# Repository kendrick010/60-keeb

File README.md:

# 60-keeb
> A 60% keyboard because why not.

## How To...
Stack Order:
- plate_1 (top most)
- plate_2
- plate_3 (switch plate)
- plate_4
- plate_5
- plate_6 (bottom most)

## BOM
| Component | Vendor | Quantity|
| --------- | ------ | ------- |
| PCB | -------- | 1 |
| ATMEGA32U4 | [Digikey](https://www.digikey.com/en/products/detail/microchip-technology/ATMEGA32U4RC-MUR/2507985) | 1 |
| USB Mini B Port | [Digikey](https://www.digikey.com/en/products/detail/edac-inc/690-005-299-043/4312191) | 1 |
| Tactile SMD Switch | [Digikey](https://www.digikey.com/en/products/detail/e-switch/TL3342F160QG-TR/379004) | 1 |
| 1N4148 SMD Diode | [Digikey](https://www.digikey.com/en/products/detail/smc-diode-solutions/1N4148WTR/6022450) | 63 |
| 16MHz SMD Cystal | [Digikey](https://www.digikey.com/en/products/detail/ecs-inc./ECS-160-12-33-AGM-TR/9648950?utm_adgroup=Crystals&utm_source=google&utm_medium=cpc&utm_campaign=Shopping_Product_Crystals%2C%20Oscillators%2C%20Resonators_NEW&utm_term=&utm_content=Crystals&gclid=CjwKCAjwloCSBhAeEiwA3hVo_cbyDTwI6-S_fugYXFgKN49tR0nGhBOCDoLL6SpNIffyFdOyPNAKBRoCRlkQAvD_BwE) | 1 |
| 22Ω SMD Resistor | [Digikey](https://www.digikey.com/en/products/detail/stackpole-electronics-inc/RMCF0805JT22R0/1942533) | 2 |
| 10kΩ SMD Resistor | [Digikey](https://www.digikey.com/en/products/detail/stackpole-electronics-inc/RMCF0805JT10K0/1942577) | 2 |
| 0.1uF Ceramic SMD Capacitor | [Digikey](https://www.digikey.com/en/products/detail/kyocera-avx/08055F104K4T2A/1024871?s=N4IgTCBcDaICwHYAcBaAzANgIxxVlAcgCIgC6AvkA) | 4 |
| 1uF Ceramic SMD Capacitor | [Digikey](https://www.digikey.com/en/products/detail/yageo/CC0805KKX7R8BB105/2833621) | 1 |
| 4.7uF Ceramic SMD Capacitor | [Digikey](https://www.digikey.com/en/products/detail/samsung-electro-mechanics/CL21A475KAQNNNE/3886902) | 1 |
| 22pF Ceramic SMD Capacitor | [Digikey](https://www.digikey.com/en/products/detail/kemet/C0805C220J5GACTU/411388) | 2 |
| M2x16mm Standoffs | [Amazon](https://www.amazon.com/dp/B07768Q7YS?psc=1&ref=ppx_yo2ov_dt_b_product_details) | 8 |
| M2 Screws | [Amazon](https://www.amazon.com/dp/B07768Q7YS?psc=1&ref=ppx_yo2ov_dt_b_product_details) | 8 |

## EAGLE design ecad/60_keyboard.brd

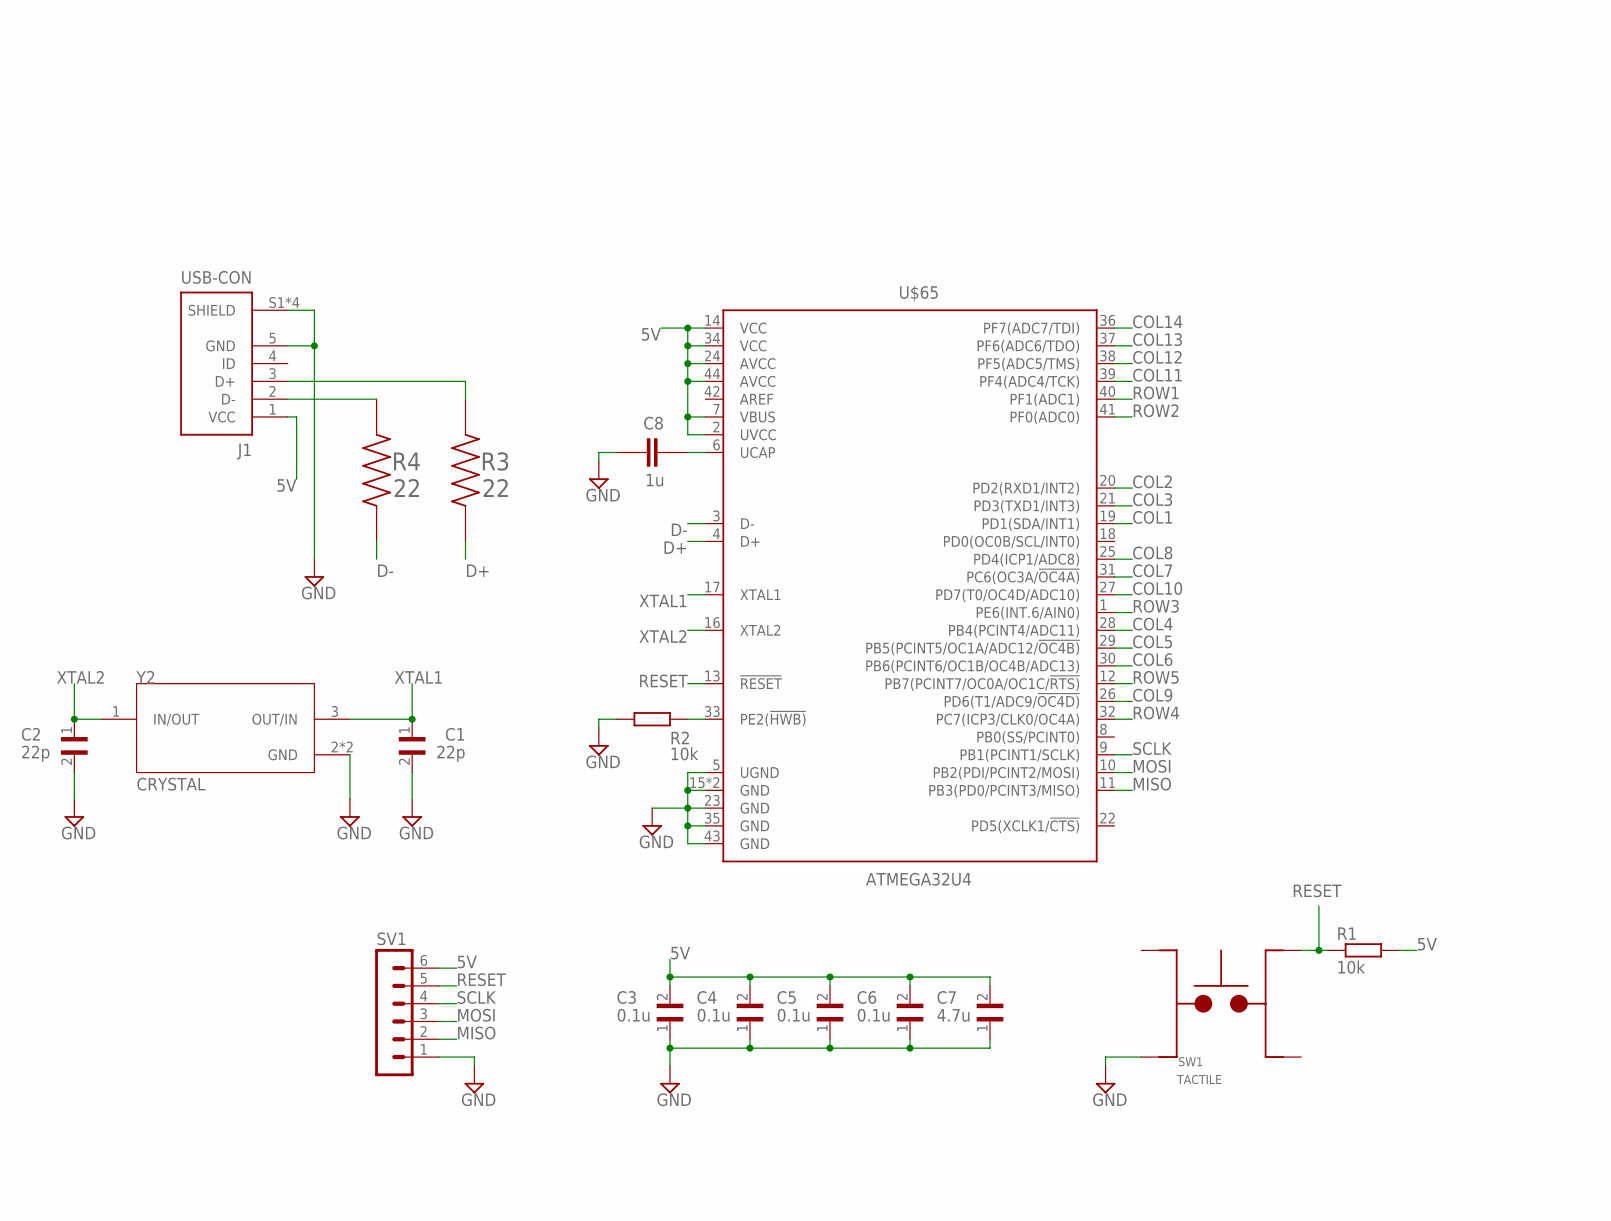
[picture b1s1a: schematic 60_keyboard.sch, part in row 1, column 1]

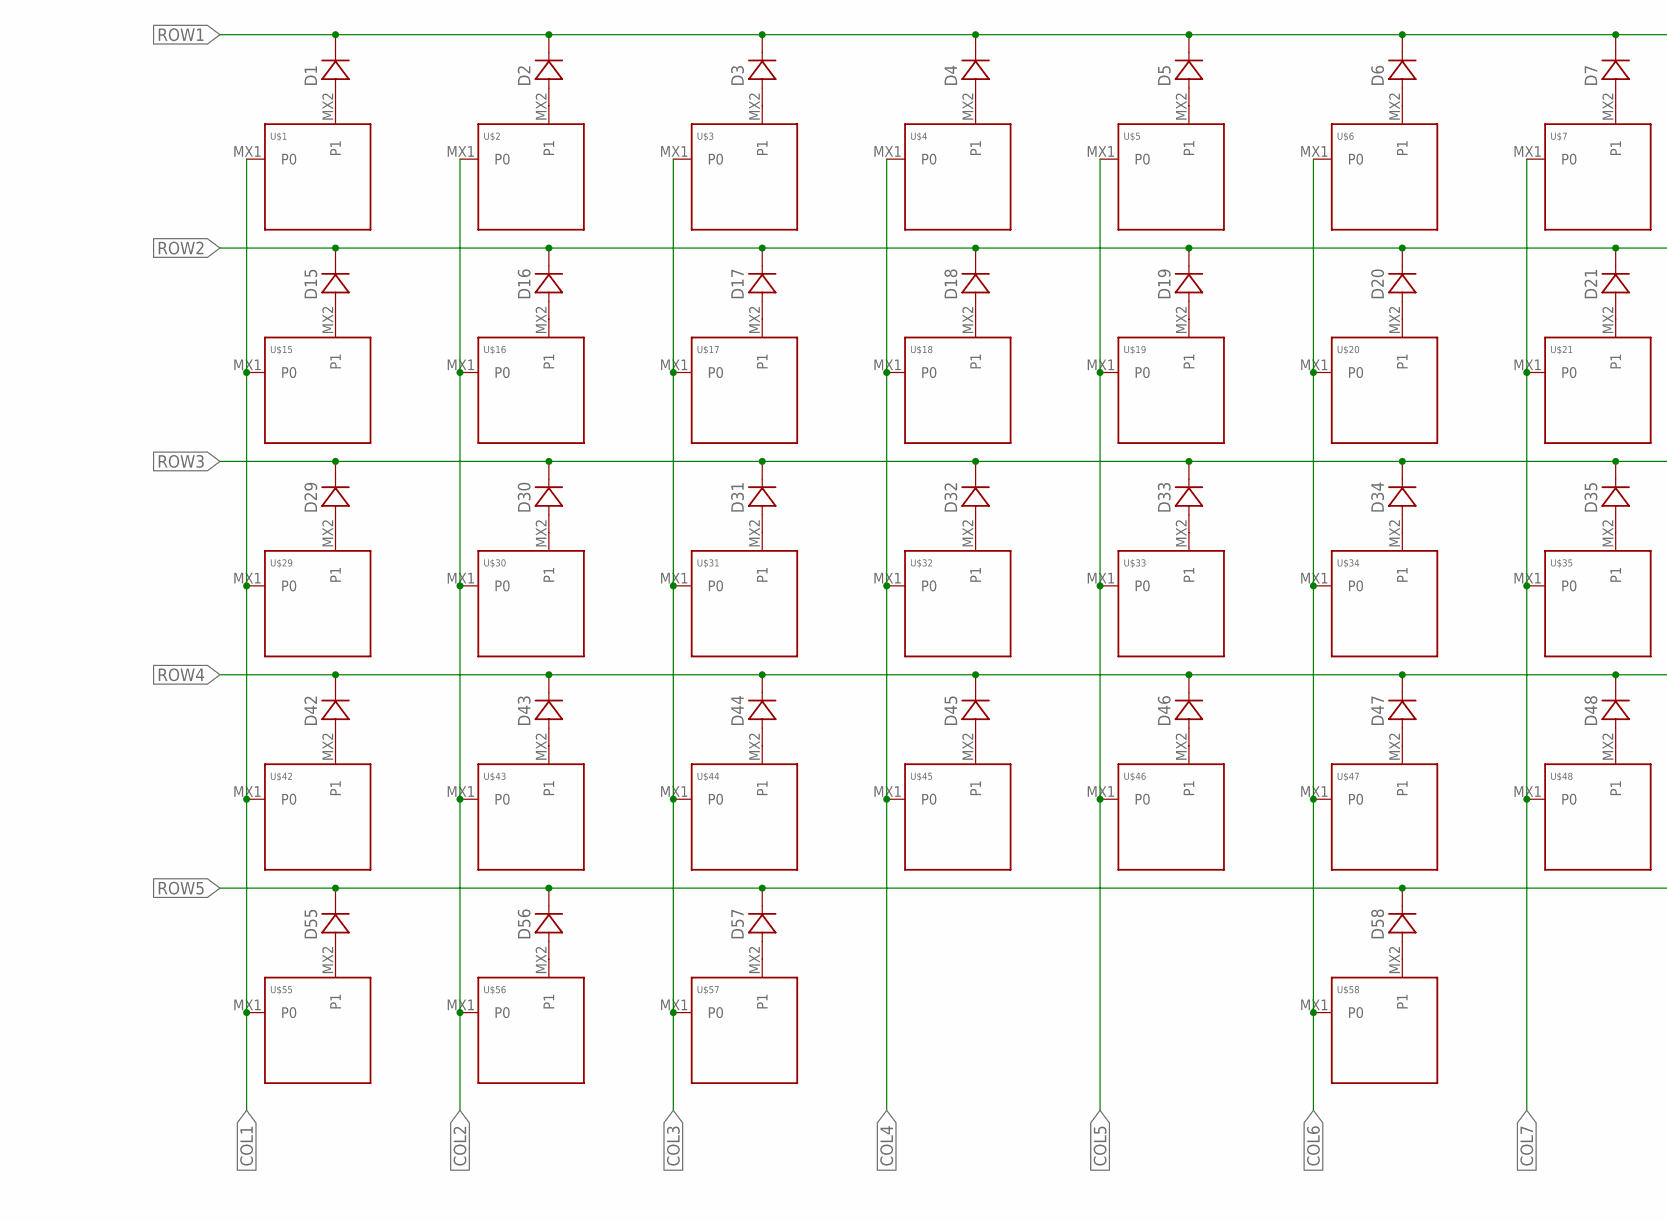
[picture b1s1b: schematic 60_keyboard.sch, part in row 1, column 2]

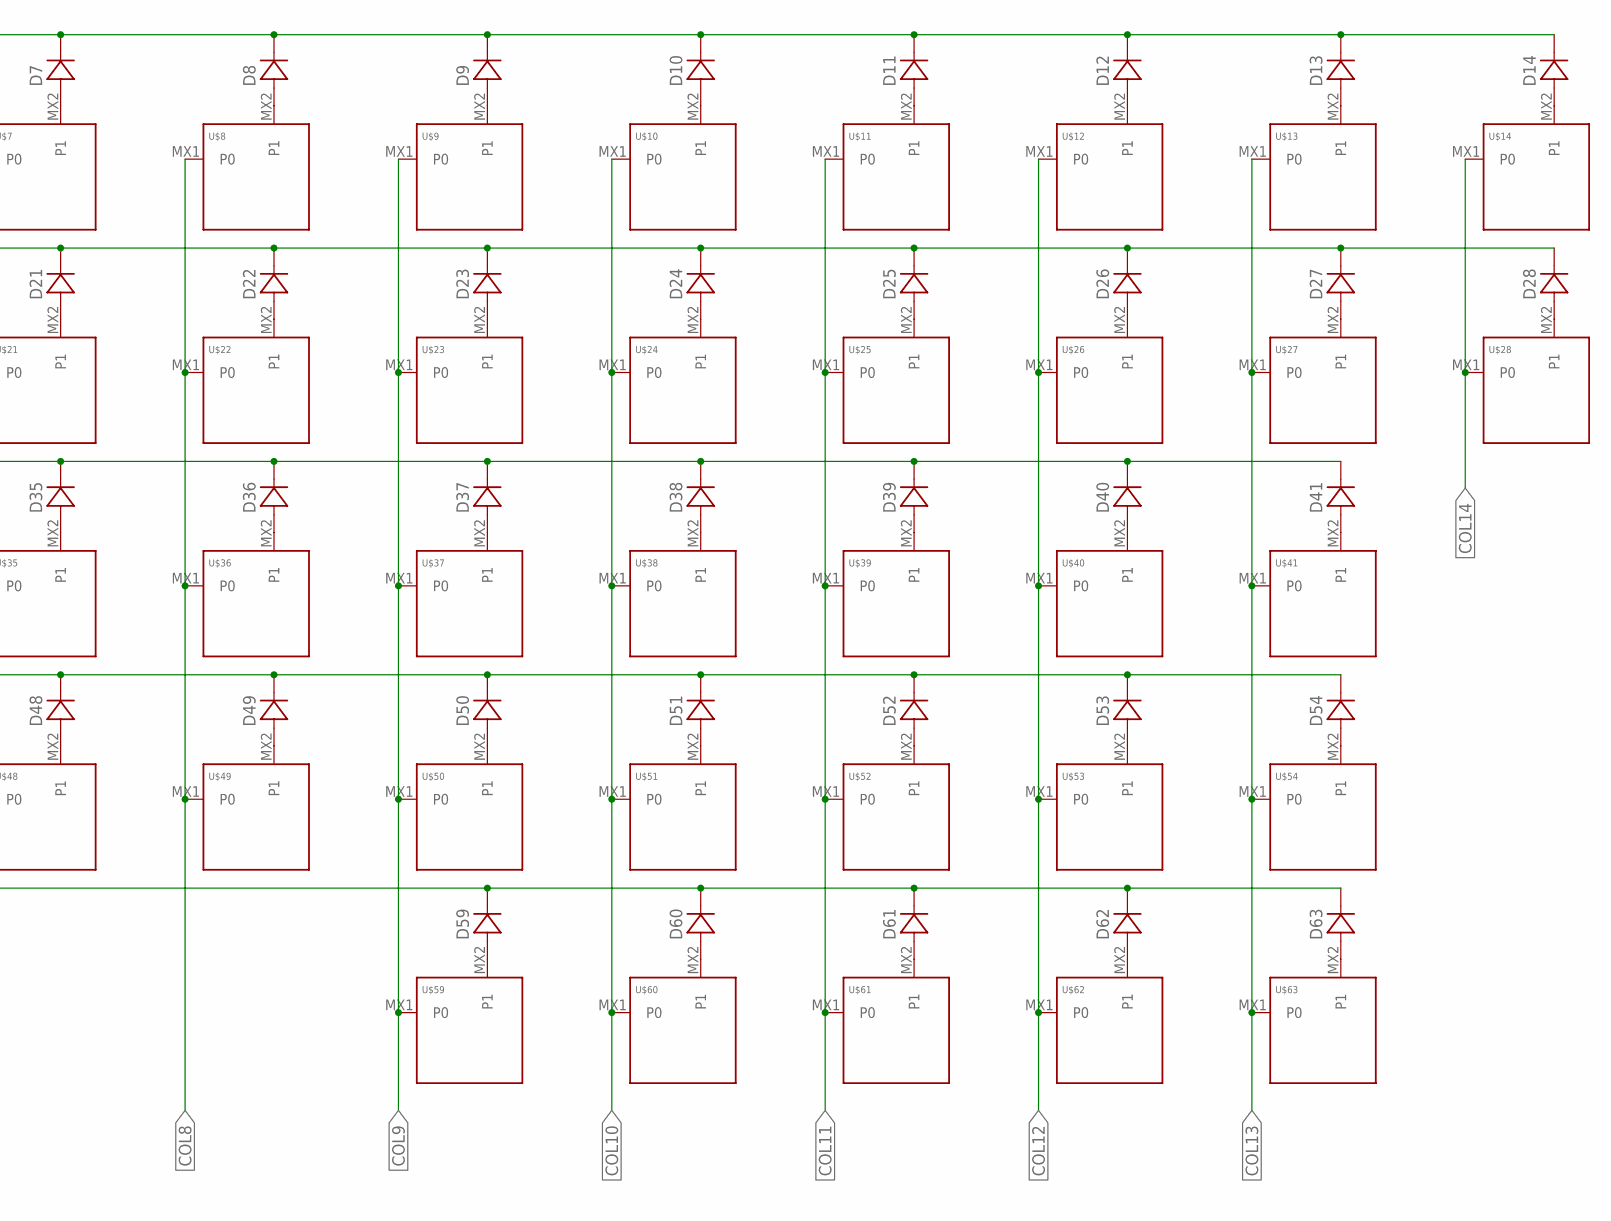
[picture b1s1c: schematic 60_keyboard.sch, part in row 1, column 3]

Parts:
C1, C2: 22p; CAPC2012X140N
C3, C4, C5, C6: 0.1u; CAPC2012X140N
C7: 4.7u; CAPC2012X140N
C8: 1u; C0805
D1, D2, D3, D4, D5, D6, D7, D8, D9, D10, D11, D12, D13, D14, D15, D16, D17, D18, D19, D20, D21, D22, D23, D24, D25, D26, D27, D28, D29, D30, D31, D32, D33, D34, D35, D36, D37, D38, D39, D40, D41, D42, D43, D44, D45, D46, D47, D48, D49, D50, D51, D52, D53, D54, D55, D56, D57, D58, D59, D60, D61, D62, D63: DIODE-SOD-123; SOD-123
J1: USB-CON; EDAC_690-005-299-043
R1, R2: 10k; R0805
R3, R4: 22; RESC2012X65N
SV1: MA06-1
SW1: TACTILE; SW_TL3342F160QG/TR
U$1, U$2, U$3, U$4, U$5, U$6, U$7, U$8, U$9, U$10, U$11, U$12, U$13, U$15, U$16, U$17, U$18, U$19, U$20, U$21, U$22, U$23, U$24, U$25, U$26, U$27, U$28, U$29, U$30, U$31, U$32, U$33, U$34, U$35, U$36, U$37, U$38, U$39, U$40, U$43, U$44, U$45, U$46, U$47, U$48, U$49, U$50, U$51, U$52, U$53, U$54, U$55, U$56, U$57, U$59, U$60, U$61, U$62, U$63: KEYSWITCH-PLAIN-MXHSPCB-1U; MXHSPCB-1U
U$14, U$41, U$42: KEYSWITCH-PLAIN-MXHSPCB-2U; MXHSPCB-2U
U$58: KEYSWITCH-PLAIN-MXHSPCB-6.25U-FLIPPED; MXHSPCB-6.25U-FLIPPED
U$65: ATMEGA32U4; QFN-44
Y2: CRYSTAL; XTAL_ECS-160-12-33-AGN-TR

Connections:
5V: C3.2, C4.2, C5.2, C6.2, C7.2, J1.1 (VCC), R1.2, SV1.6, U$65.2 (UVCC), U$65.7 (VBUS), U$65.14 (VCC), U$65.24 (AVCC), U$65.34 (VCC), U$65.44 (AVCC)
COL1: U$1.MX1 (P0), U$15.MX1 (P0), U$29.MX1 (P0), U$42.MX1 (P0), U$55.MX1 (P0), U$65.19 (PD1(SDA/INT1))
COL2: U$2.MX1 (P0), U$16.MX1 (P0), U$30.MX1 (P0), U$43.MX1 (P0), U$56.MX1 (P0), U$65.20 (PD2(RXD1/INT2))
COL3: U$3.MX1 (P0), U$17.MX1 (P0), U$31.MX1 (P0), U$44.MX1 (P0), U$57.MX1 (P0), U$65.21 (PD3(TXD1/INT3))
COL4: U$4.MX1 (P0), U$18.MX1 (P0), U$32.MX1 (P0), U$45.MX1 (P0), U$65.28 (PB4(PCINT4/ADC11))
COL5: U$5.MX1 (P0), U$19.MX1 (P0), U$33.MX1 (P0), U$46.MX1 (P0), U$65.29 (PB5(PCINT5/OC1A/ADC12/!OC4B))
COL6: U$6.MX1 (P0), U$20.MX1 (P0), U$34.MX1 (P0), U$47.MX1 (P0), U$58.MX1 (P0), U$65.30 (PB6(PCINT6/OC1B/OC4B/ADC13))
COL7: U$7.MX1 (P0), U$21.MX1 (P0), U$35.MX1 (P0), U$48.MX1 (P0), U$65.31 (PC6(OC3A/!OC4A))
COL8: U$8.MX1 (P0), U$22.MX1 (P0), U$36.MX1 (P0), U$49.MX1 (P0), U$65.25 (PD4(ICP1/ADC8))
COL9: U$9.MX1 (P0), U$23.MX1 (P0), U$37.MX1 (P0), U$50.MX1 (P0), U$59.MX1 (P0), U$65.26 (PD6(T1/ADC9/!OC4D))
COL10: U$10.MX1 (P0), U$24.MX1 (P0), U$38.MX1 (P0), U$51.MX1 (P0), U$60.MX1 (P0), U$65.27 (PD7(T0/OC4D/ADC10))
COL11: U$11.MX1 (P0), U$25.MX1 (P0), U$39.MX1 (P0), U$52.MX1 (P0), U$61.MX1 (P0), U$65.39 (PF4(ADC4/TCK))
COL12: U$12.MX1 (P0), U$26.MX1 (P0), U$40.MX1 (P0), U$53.MX1 (P0), U$62.MX1 (P0), U$65.38 (PF5(ADC5/TMS))
COL13: U$13.MX1 (P0), U$27.MX1 (P0), U$41.MX1 (P0), U$54.MX1 (P0), U$63.MX1 (P0), U$65.37 (PF6(ADC6/TDO))
COL14: U$14.MX1 (P0), U$28.MX1 (P0), U$65.36 (PF7(ADC7/TDI))
D+: R3.1, U$65.4 (D+)
D-: R4.1, U$65.3 (D-)
GND: C1.2, C2.2, C3.1, C4.1, C5.1, C6.1, C7.1, C8.2, J1.5 (GND), J1.S1 (SHIELD), J1.S2 (SHIELD), J1.S3 (SHIELD), J1.S4 (SHIELD), R2.1, SV1.1, SW1.3, U$65.5 (UGND), U$65.15 (GND), U$65.23 (GND), U$65.35 (GND), U$65.43 (GND), U$65.TAB (GND), Y2.2 (GND), Y2.4 (GND)
MISO: SV1.2, U$65.11 (PB3(PD0/PCINT3/MISO))
MOSI: SV1.3, U$65.10 (PB2(PDI/PCINT2/MOSI))
unnamed: D1.A, U$1.MX2 (P1)
unnamed: D2.A, U$2.MX2 (P1)
unnamed: D3.A, U$3.MX2 (P1)
unnamed: D4.A, U$4.MX2 (P1)
unnamed: D5.A, U$5.MX2 (P1)
unnamed: D6.A, U$6.MX2 (P1)
unnamed: D7.A, U$7.MX2 (P1)
unnamed: D8.A, U$8.MX2 (P1)
unnamed: D9.A, U$9.MX2 (P1)
unnamed: D10.A, U$10.MX2 (P1)
unnamed: D11.A, U$11.MX2 (P1)
unnamed: D12.A, U$12.MX2 (P1)
unnamed: D13.A, U$13.MX2 (P1)
unnamed: D14.A, U$14.MX2 (P1)
unnamed: D15.A, U$15.MX2 (P1)
unnamed: D16.A, U$16.MX2 (P1)
unnamed: D17.A, U$17.MX2 (P1)
unnamed: D18.A, U$18.MX2 (P1)
unnamed: D19.A, U$19.MX2 (P1)
unnamed: D20.A, U$20.MX2 (P1)
unnamed: D21.A, U$21.MX2 (P1)
unnamed: D22.A, U$22.MX2 (P1)
unnamed: D23.A, U$23.MX2 (P1)
unnamed: D24.A, U$24.MX2 (P1)
unnamed: D25.A, U$25.MX2 (P1)
unnamed: D26.A, U$26.MX2 (P1)
unnamed: D27.A, U$27.MX2 (P1)
unnamed: D28.A, U$28.MX2 (P1)
unnamed: D29.A, U$29.MX2 (P1)
unnamed: D30.A, U$30.MX2 (P1)
unnamed: D31.A, U$31.MX2 (P1)
unnamed: D32.A, U$32.MX2 (P1)
unnamed: D33.A, U$33.MX2 (P1)
unnamed: D34.A, U$34.MX2 (P1)
unnamed: D35.A, U$35.MX2 (P1)
unnamed: D36.A, U$36.MX2 (P1)
unnamed: D37.A, U$37.MX2 (P1)
unnamed: D38.A, U$38.MX2 (P1)
unnamed: D39.A, U$39.MX2 (P1)
unnamed: D40.A, U$40.MX2 (P1)
unnamed: D41.A, U$41.MX2 (P1)
unnamed: D42.A, U$42.MX2 (P1)
unnamed: D43.A, U$43.MX2 (P1)
unnamed: D44.A, U$44.MX2 (P1)
unnamed: D45.A, U$45.MX2 (P1)
unnamed: D46.A, U$46.MX2 (P1)
unnamed: D47.A, U$47.MX2 (P1)
unnamed: D48.A, U$48.MX2 (P1)
unnamed: D49.A, U$49.MX2 (P1)
unnamed: D50.A, U$50.MX2 (P1)
unnamed: D51.A, U$51.MX2 (P1)
unnamed: D52.A, U$52.MX2 (P1)
unnamed: D53.A, U$53.MX2 (P1)
unnamed: D54.A, U$54.MX2 (P1)
unnamed: D58.A, U$58.MX2 (P1)
unnamed: D55.A, U$55.MX2 (P1)
unnamed: D56.A, U$56.MX2 (P1)
unnamed: D57.A, U$57.MX2 (P1)
unnamed: J1.2 (D-), R4.2
unnamed: D59.A, U$59.MX2 (P1)
unnamed: D60.A, U$60.MX2 (P1)
unnamed: D61.A, U$61.MX2 (P1)
unnamed: D62.A, U$62.MX2 (P1)
unnamed: D63.A, U$63.MX2 (P1)
unnamed: J1.3 (D+), R3.2
unnamed: R2.2, U$65.33 (PE2(!HWB))
unnamed: C8.1, U$65.6 (UCAP)
RESET: R1.1, SV1.5, SW1.2, U$65.13 (!RESET)
ROW1: D1.C, D2.C, D3.C, D4.C, D5.C, D6.C, D7.C, D8.C, D9.C, D10.C, D11.C, D12.C, D13.C, D14.C, U$65.40 (PF1(ADC1))
ROW2: D15.C, D16.C, D17.C, D18.C, D19.C, D20.C, D21.C, D22.C, D23.C, D24.C, D25.C, D26.C, D27.C, D28.C, U$65.41 (PF0(ADC0))
ROW3: D29.C, D30.C, D31.C, D32.C, D33.C, D34.C, D35.C, D36.C, D37.C, D38.C, D39.C, D40.C, D41.C, U$65.1 (PE6(INT.6/AIN0))
ROW4: D42.C, D43.C, D44.C, D45.C, D46.C, D47.C, D48.C, D49.C, D50.C, D51.C, D52.C, D53.C, D54.C, U$65.32 (PC7(ICP3/CLK0/OC4A))
ROW5: D55.C, D56.C, D57.C, D58.C, D59.C, D60.C, D61.C, D62.C, D63.C, U$65.12 (PB7(PCINT7/OC0A/OC1C/!RTS))
SCLK: SV1.4, U$65.9 (PB1(PCINT1/SCLK))
XTAL1: C1.1, U$65.17 (XTAL1), Y2.3 (OUT/IN)
XTAL2: C2.1, U$65.16 (XTAL2), Y2.1 (IN/OUT)

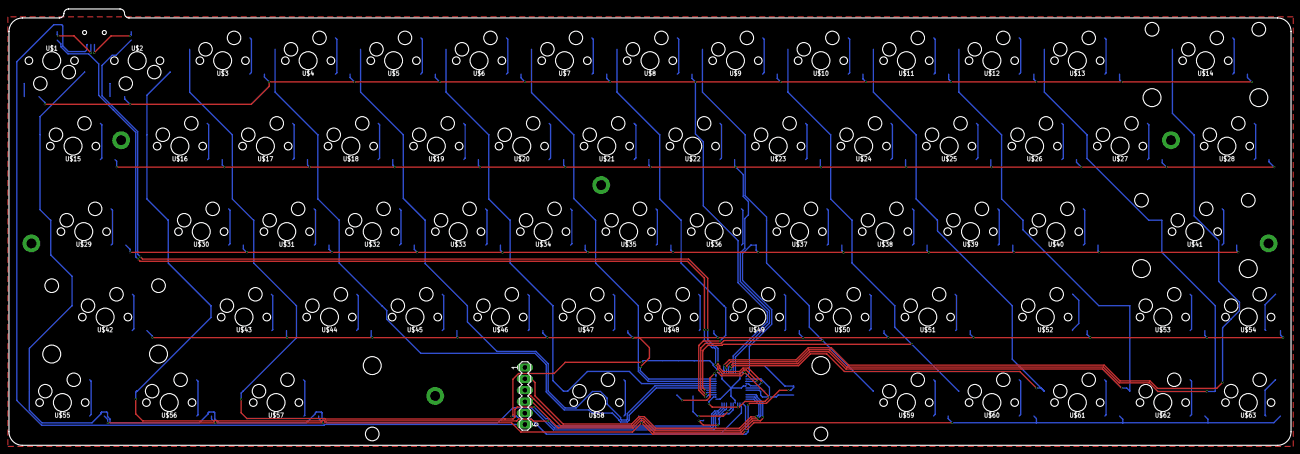
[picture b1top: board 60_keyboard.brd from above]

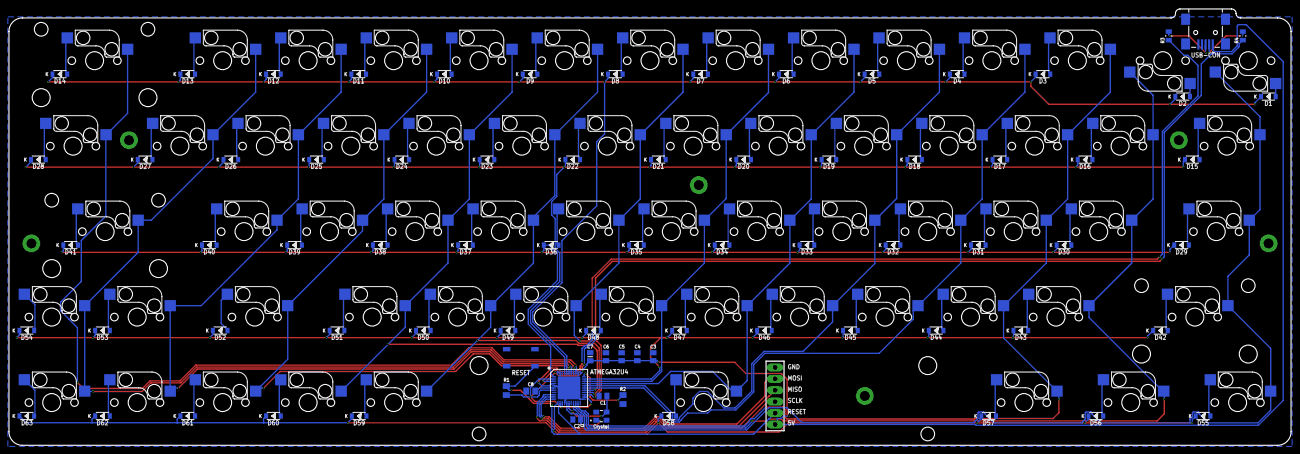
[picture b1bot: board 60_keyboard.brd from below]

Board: 2 copper layers, 285.8 x 97.2 mm, 143 parts (142 on the bottom side), 96 nets.

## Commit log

2021-12-13 updated layout
2021-12-13 ignore DS store
2021-12-13 BOM removed
2021-12-16 case model and files
2021-12-16 remove ds store
2022-03-23 new layout
2022-03-26 ecad
2022-03-27 ecad, gebers
2022-03-28 case files
2022-03-31 laser cut files
2022-04-27 firmware
2022-04-27 readme
2022-05-13 assembly
